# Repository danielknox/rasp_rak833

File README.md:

# rasp_rak833
Shield containing rak833 for rasp pi. RAK833 and GPS on the board have been tested and are functional. I've still to test the temp/humidity sensor (coming tomorrow). I also need to test RF performance.

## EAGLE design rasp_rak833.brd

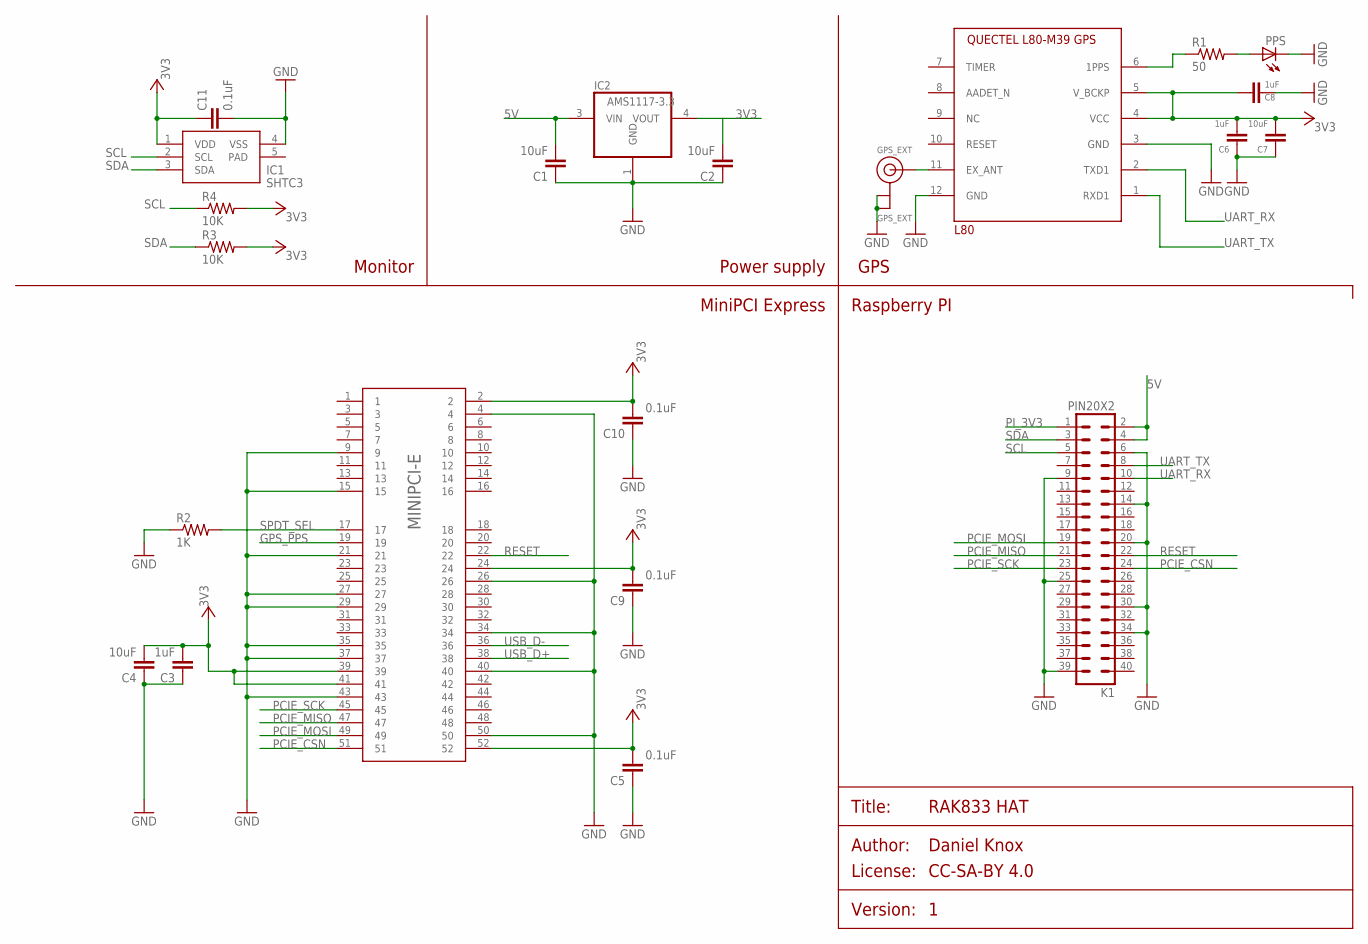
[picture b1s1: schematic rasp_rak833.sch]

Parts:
C1, C2, C4, C7: 10uF; 0805
C3, C6, C8: 1uF; 0805
C5, C9, C10, C11: 0.1uF; 0805
GPS_EXT: GPS_EXT; U.FL
IC1: SHTC3
IC2: AMS1117-3.3; SOT223
K1: PIN20X2; PIN_20X2
L80: L80_GNSS_MODULE; L80_PACKAGE
MINIPCI-E: MINI-PCIE-RAW; 67910-MINI-PCIE
PPS: LEDCHIP-LED0805; CHIP-LED0805
R1: 50; R0805
R2: 1K; R0805
R3, R4: 10K; R0805

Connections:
3V3: C2.2, C3.2, C4.2, C5.2, C6.2, C7.2, C8.2, C9.2, C10.2, IC2.4 (VOUT), L80.4 (VCC), L80.5 (V_BCKP), MINIPCI-E.2, MINIPCI-E.24, MINIPCI-E.39, MINIPCI-E.41, MINIPCI-E.52
5V: C1.2, IC2.3 (VIN), K1.2, K1.4
GND: C1.1, C2.1, C3.1, C4.1, C5.1, C6.1, C7.1, C8.1, C9.1, C10.1, C11.2, GPS_EXT.1 (GND), GPS_EXT.2 (GND), IC1.4 (VSS), IC2.1 (GND), K1.6, K1.9, K1.14, K1.20, K1.25, K1.30, K1.34, K1.39, L80.3 (GND), L80.12 (GND), MINIPCI-E.4, MINIPCI-E.9, MINIPCI-E.15, MINIPCI-E.21, MINIPCI-E.26, MINIPCI-E.27, MINIPCI-E.29, MINIPCI-E.34, MINIPCI-E.35, MINIPCI-E.37, MINIPCI-E.40, MINIPCI-E.43, MINIPCI-E.50, PPS.C, R2.1
GPS_PPS: L80.6 (1PPS), MINIPCI-E.19, R1.1
unnamed: GPS_EXT.3 (SIGNAL), L80.11 (EX_ANT)
unnamed: PPS.A, R1.2
PCIE_CSN: K1.24, MINIPCI-E.51
PCIE_MISO: K1.21, MINIPCI-E.47
PCIE_MOSI: K1.19, MINIPCI-E.49
PCIE_SCK: K1.23, MINIPCI-E.45
PI_3V3: C11.1, IC1.1 (VDD), K1.1, R3.2, R4.2
RESET: K1.22, MINIPCI-E.22
SCL: IC1.2 (SCL), K1.5, R4.1
SDA: IC1.3 (SDA), K1.3, R3.1
SPDT_SEL: MINIPCI-E.17, R2.2
UART_RX: K1.10, L80.2 (TXD1)
UART_TX: K1.8, L80.1 (RXD1)
USB_D+: MINIPCI-E.38
USB_D-: MINIPCI-E.36

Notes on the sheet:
MiniPCI Express
Raspberry PI
Power supply
GPS
Monitor

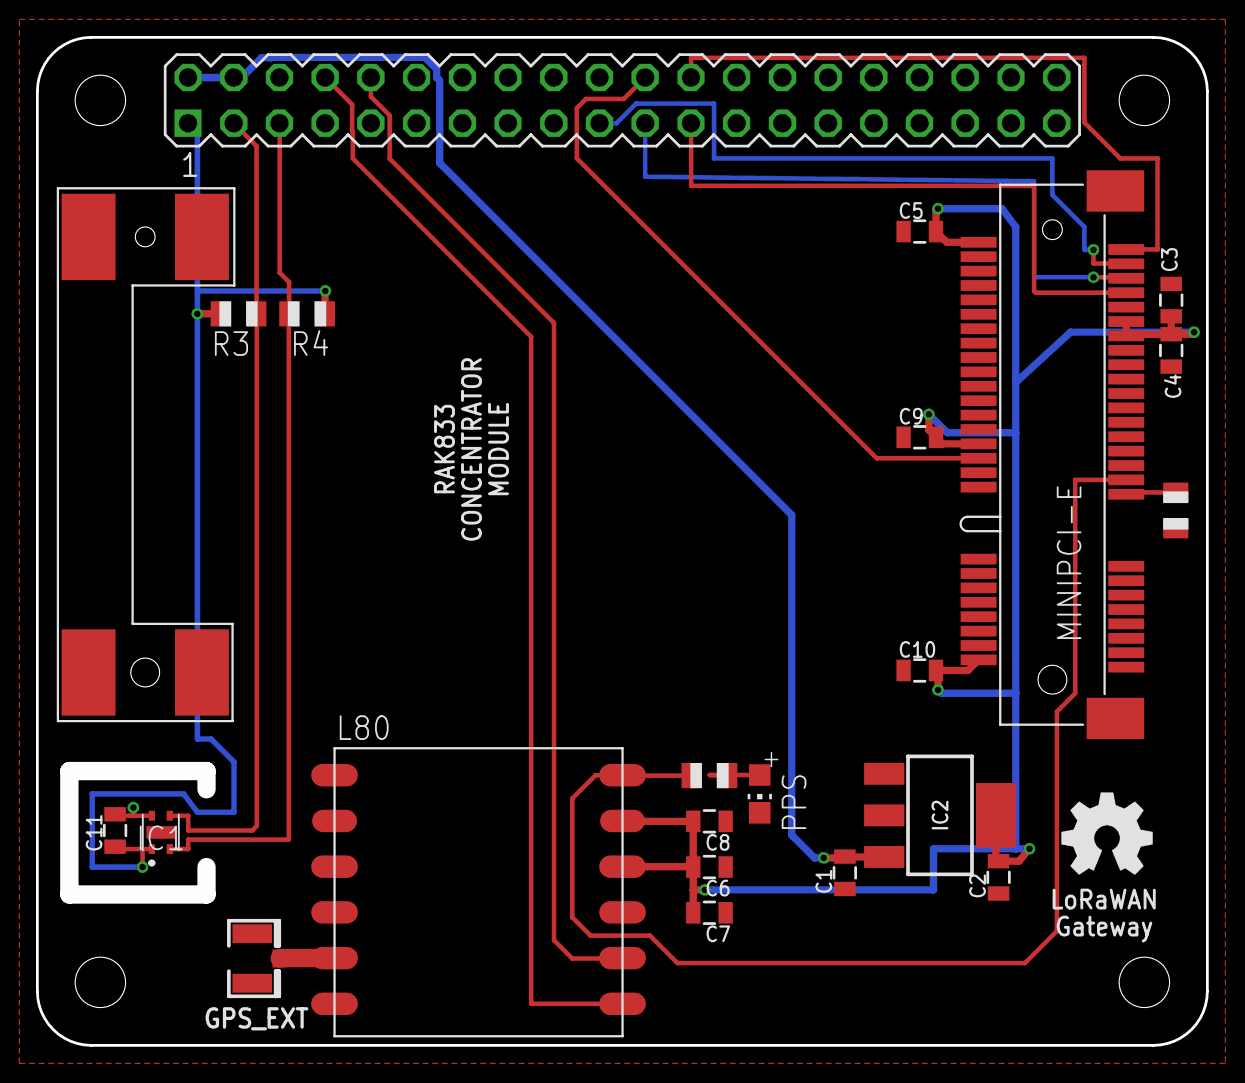
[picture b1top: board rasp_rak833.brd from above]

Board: 2 copper layers, 65.0 x 56.0 mm, 22 parts (0 on the bottom side), 17 nets.

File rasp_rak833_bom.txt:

Part      Value           Device          Package         Description                                              
C1        10uF            C-EU0805        0805            CAPACITOR, European symbol                                                                                                                                                                                                                     
C2        10uF            C-EU0805        0805            CAPACITOR, European symbol                                                                                                                                                                                                                     
C3        1uF             C-EU0805        0805            CAPACITOR, European symbol                                                                                                                                                                                                                     
C4        10uF            C-EU0805        0805            CAPACITOR, European symbol                                                                                                                                                                                                                     
C5        0.1uF           C-EU0805        0805            CAPACITOR, European symbol                                                                                                                                                                                                                     
C6        1uF             C-EU0805        0805            CAPACITOR, European symbol                                                                                                                                                                                                                     
C7        10uF            C-EU0805        0805            CAPACITOR, European symbol                                                                                                                                                                                                                     
C8        1uF             C-EU0805        0805            CAPACITOR, European symbol                                                                                                                                                                                                                     
C9        0.1uF           C-EU0805        0805            CAPACITOR, European symbol                                                                                                                                                                                                                     
C10       0.1uF           C-EU0805        0805            CAPACITOR, European symbol                                                                                                                                                                                                                     
C11       0.1uF           C-EU0805        0805            CAPACITOR, European symbol                                                                                                                                                                                                                     
GPS_EXT   GPS_EXT         ANTENNA_U.FL    U.FL            U.FL Antenna Connector                                                                                                                                                                                                                         
IC1       SHTC3           SHTC3           SHTC3           Humidity and Temperature Sensor IC                       
IC2       AMS1117-3.3     REG1117SOT223-2 SOT223          800mA and 1A Low Dropout (LDO) Positive Regulator                                                                                                                                                                                              
K1        PIN20X2         PIN20X2         PIN_20X2                                                                                                                                                                                                                                                       
L80       L80_GNSS_MODULE L80_GNSS_MODULE L80_PACKAGE     GPS module with an embedded patch antenna (15mmx15mmx4mm)                                                                                                                                                                                      
MINIPCI-E                 MINI-PCIE-RAW   67910-MINI-PCIE Mini PCI-E card                                                                                                                                                                                                                                
PPS                       LEDCHIP-LED0805 CHIP-LED0805    LED                                                                                                                                                                                                                                            
R1        50              R-US_R0805      R0805           RESISTOR, American symbol                                                                                                                                                                                                                      
R2        1K              R-US_R0805      R0805           RESISTOR, American symbol                                                                                                                                                                                                                      
R3        10K             R-US_R0805      R0805           RESISTOR, American symbol       -- Likely not needed as pi I2c has pullups                                                                                                                                                                                                               
R4        10K             R-US_R0805      R0805           RESISTOR, American symbol       -- Likely not needed as pi I2c has pullups

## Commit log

2018-07-26 Board tested. Minor resistor value tweaks
2018-08-06 cap revisions
2018-10-26 Update LICENSE
    As this is not code, GPL is unsuitable. As such I've applied a license that is appropriate to this content. Please note the non-commericial aspect on this license.

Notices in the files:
rasp_rak833.sch:
PROJECT_LICENSE: CC-SA-BY 4.0
parts and their libraries:
SparkFun-Aesthetics: Licensing: Creative Commons ShareAlike 4.0 International - https://creativecommons.org/licenses/by-sa/4.0
